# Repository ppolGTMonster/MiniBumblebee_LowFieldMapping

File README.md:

# Easy Scalable, Low-Cost Open Source Magnetic Field Detection System for Evaluating Low-Field MRI Magnets using a Motion Tracked Robot

## Author:
Pavel Povolni <pavel.povolni@tuebingen.mpg.de>

## Other Contributors to this hard- and software:
Felix Glang
  *  https://github.com/fglang
  * helped with the optimizers to design the hardware (fmincon & genetic)

Praveen Valsala
  * https://github.com/praveenivp
  * helped with reconstruction of MRI Data

Florian Birk
  * https://github.com/birkfl
  * helped with the Motion Tracking & the openCV Library

Sergej Maltsev
  * https://github.com/TheWinterProgrammer
  * helped with the Hardware 

## How to use

We tried our best to make the hardware as reproducible as possible and to develop the software without expensive extra toolboxes in Matlab (data evaluation), Python (motion tracking) and C++ (embedded code).
The PCBs were designed in KiCad 7 (free).
The mechanical components were designed with Autodesk Inventor 2021, although the Step files can be opened in any other CAD tool.

To get you started with the project as easily as possible, there are 4 instruction pdf's:
* Hallsensor (description of hardware & software for the hall sensor and calibration)
* Robot (description of the hardware & software for the robot used, including control)
* Motion tracking (description of the motion tracking setup & camera, including calibration)
* Mapping (description of the measurement process)

## Name
We always refer to this robot as Mini-Bumblebee in our team. The “big” Bumblebee refers to the large cubic robot that was built. Bumblebee itself stands for:
* B-Field
* Unterstanding and
* Mapping using
* Benchmarked
* Localized Hall
* Effect-based 
* Background
* Estimation and
* Evaluation

## Citing

If you use this code, please cite the corresponding paper:

Povolni, P., Bendfeld, R., Maltsev, S. et al. Easy scalable, low-cost open-source magnetic field detection system for evaluating low-field MRI magnets using a motion-tracked robot. Magn Reson Mater Phy (2025). https://doi.org/10.1007/s10334-025-01239-1

https://link.springer.com/article/10.1007/s10334-025-01239-1

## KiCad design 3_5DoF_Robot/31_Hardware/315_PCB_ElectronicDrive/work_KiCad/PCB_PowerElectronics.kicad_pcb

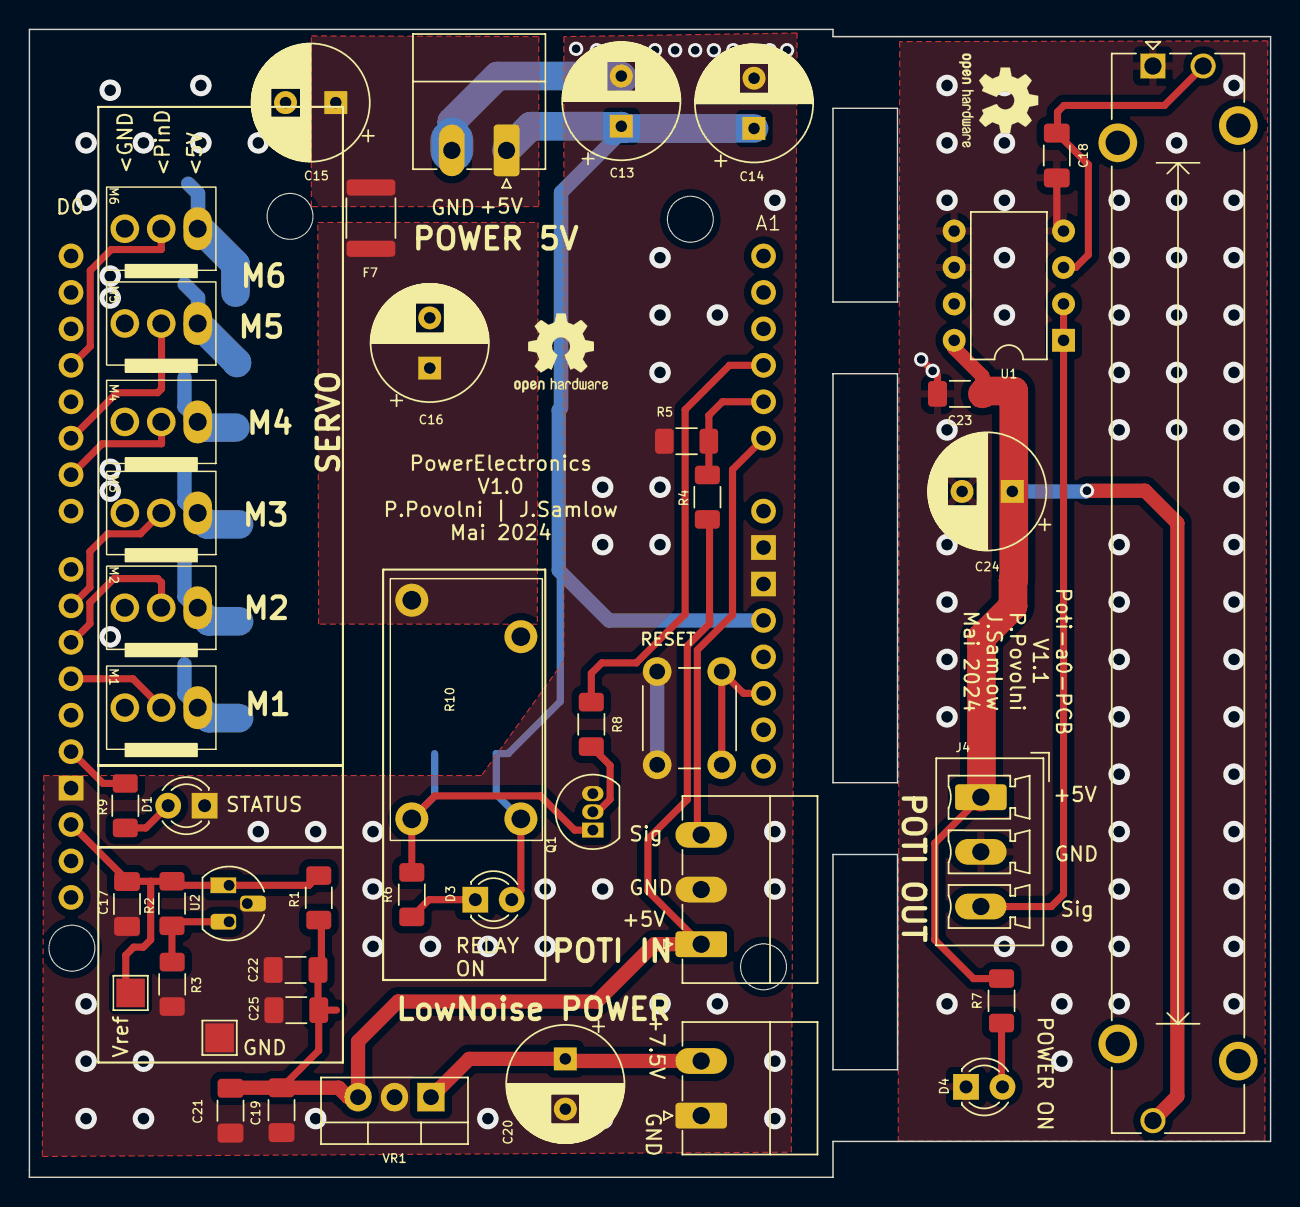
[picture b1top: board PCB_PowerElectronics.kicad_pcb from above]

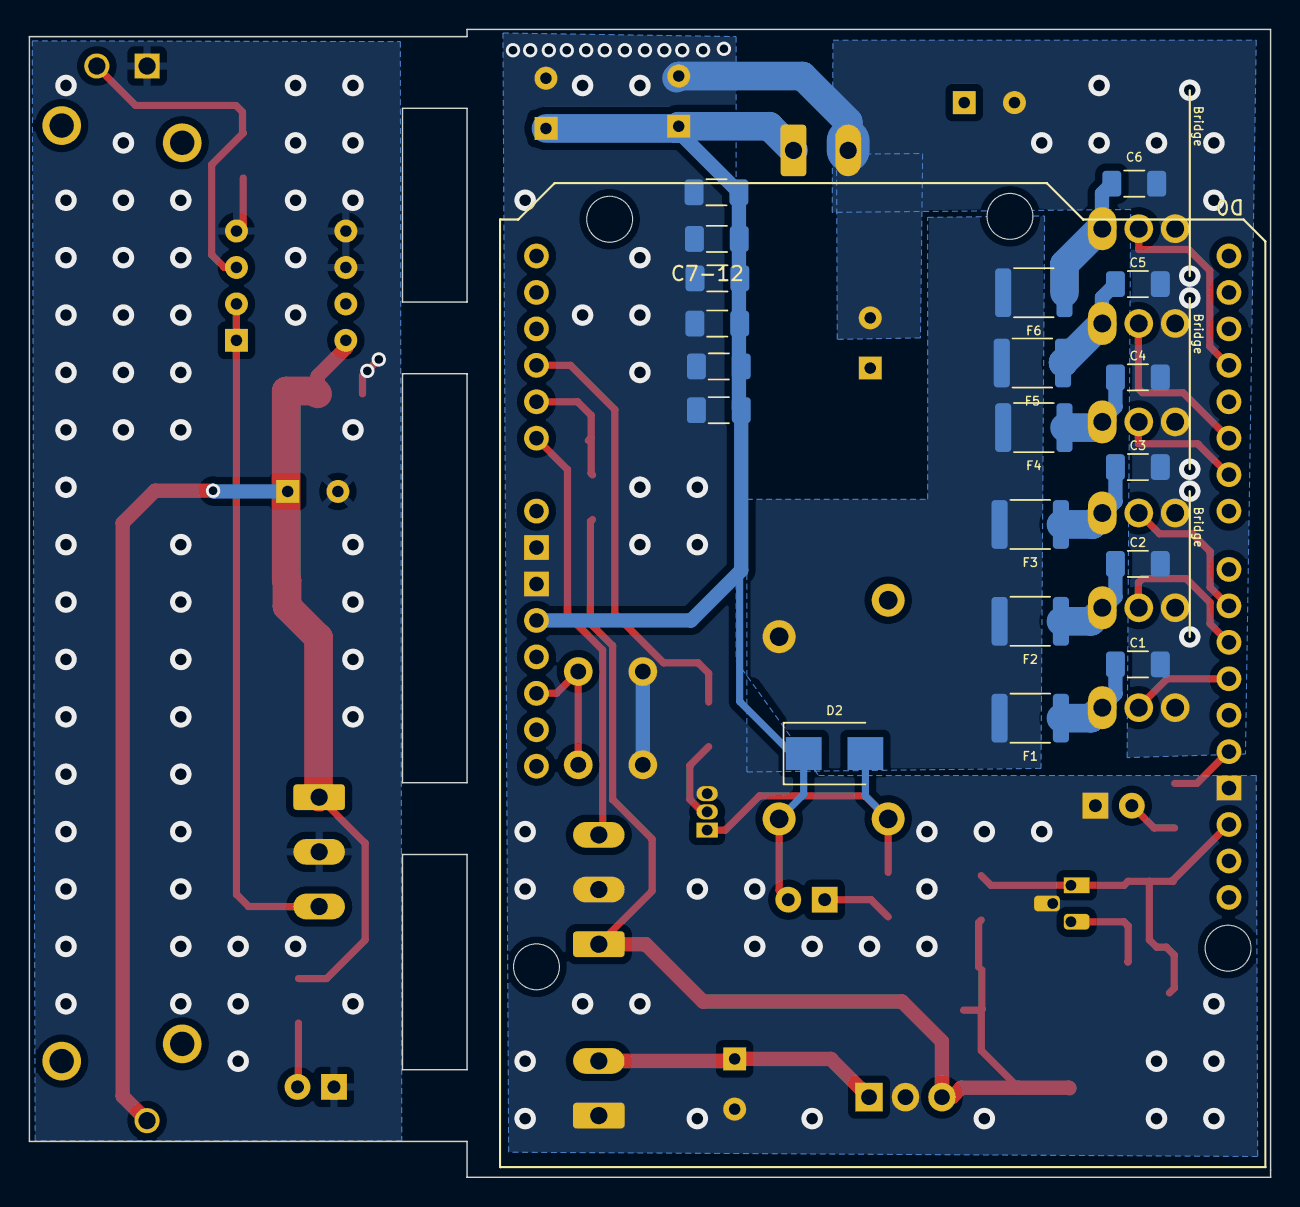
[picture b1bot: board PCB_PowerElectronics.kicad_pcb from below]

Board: 2 copper layers, 86.5 x 80.0 mm, 63 parts (19 on the bottom side), 32 nets.

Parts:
A1: Arduino_Uno; Arduino Uno Shield Mini BBB
C1, C2, C3, C4, C5, C6, C21, C25: 1µF; C_1206_3216Metric_Pad1.33x1.80mm_HandSolder
C7, C8, C9, C10, C11, C12: 100 n; C_1206_3216Metric_Pad1.33x1.80mm_HandSolder
C13, C15, C16: 47 µF; CP_Radial_D8.0mm_P3.50mm
C14, C20, C24: 47µF; CP_Radial_D8.0mm_P3.50mm
C17, C18, C19, C22, C23: 100n; C_1206_3216Metric_Pad1.33x1.80mm_HandSolder
D1: gelb; LED_D3.0mm
D2: S2A; D_SMB
D3: LED; LED_D3.0mm
D4: rot; LED_D3.0mm
F1: MF-MSMF 1100mA; Fuse_1812_4532Metric
F2, F3, F4: MF-MSMF 1100 mA; Fuse_1812_4532Metric
F5, F6, F7: MF-MSMF 750 mA; Fuse_1812_4532Metric
J1: 5V; PhoenixContact_MC_1,5_2-G-3.81_1x02_P3.81mm_Horizontal
J2: 7V; PhoenixContact_MC_1,5_2-G-3.81_1x02_P3.81mm_Horizontal
J3: Poti; PhoenixContact_MC_1,5_3-G-3.81_1x03_P3.81mm_Horizontal
J4: Poti; PhoenixContact_MCV_1,5_3-G-3.81_1x03_P3.81mm_Vertical
M1, M2, M3, M4, M5, M6: Molex_22272031; Molex_3Pin_Header
Q1: BC548A; TO-92_Inline
R1: 147, E192; R_1206_3216Metric_Pad1.30x1.75mm_HandSolder
R2: 1210, E192; R_1206_3216Metric_Pad1.30x1.75mm_HandSolder
R3, R4, R5: 2370, E192; R_1206_3216Metric_Pad1.30x1.75mm_HandSolder
R6, R7, R9: 147; R_1206_3216Metric_Pad1.30x1.75mm_HandSolder
R8: 1k; R_1206_3216Metric_Pad1.30x1.75mm_HandSolder
R10: Relay_AHQSH105LM100G
RV1: Poti; Potentiometer_Bourns_PTA6043_Single_Slide
SW1: RESET; SW_PUSH_6mm
U1: LM358; DIP-8_W7.62mm
U2: TL431C; TO-92_HandSolder
VR1: 7805; TO-220-3_Vertical

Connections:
+5V: A1.5V1 (5V), C7.1, C8.1, C9.1, C10.1, C11.1, C12.1, C13.1, C14.1, C15.1, D2.1 (K), D3.2 (A), F7.1, J1.1, R10.1
+5VA: C19.1, C21.1, C22.1, C23.1, C24.1, C25.1, J3.3, J4.1, R1.1, R4.1, R7.1, RV1.3, U1.8 (V+), VR1.3 (VO)
+5V/ Fused: C16.1, F7.2, R10.3
+5V/ Mot: F1.2, F2.2, F3.2, F4.2, F5.2, F6.2, R10.4
+7.5V: C20.1, J2.2, VR1.1 (VI)
/3,722 V (Aref): A1.AREF, C17.1, R1.2, R2.1, U2.3 (K)
/A0: A1.A0, J3.1
/A1: A1.A1, R4.2, R5.1
/A2: A1.A2, R8.1
/D3: A1.D3 (D3_INT1), M6.2
/D5: A1.D5, M5.2
/D6: A1.D6, M4.2
/D9: A1.D9, M3.2
/D10: A1.D10 (D10_CS), M2.2
/D11: A1.D11, M1.2
/D13: A1.D13, R9.1
/Poti/Pin A0: J4.3, U1.1, U1.2 (-)
GND: A1.GND1 (GND), A1.GND2 (GND), A1.GND3 (GND), C1.2, C2.2, C3.2, C4.2, C5.2, C6.2, C7.2, C8.2, C9.2, C10.2, C11.2, C12.2, C13.2, C14.2, C15.2, C16.2, C17.2, C18.2, C19.2, C20.2, C21.2, C22.2, C23.2, C24.2, C25.2, D1.1 (K), D4.1 (K), J1.2, J2.1, J3.2, J4.2, M1.3, M2.3, M3.3, M4.3, M5.3, M6.3, Q1.3 (E), R3.2, R5.2, RV1.1, SW1.2 (D), U1.4 (V-), U1.5 (+), U1.6 (-), U2.2 (A), VR1.2 (GND)
unnamed: A1.RST1 (RESET), SW1.1 (C)
unnamed: D1.2 (A), R9.2
unnamed: D2.2 (A), Q1.1 (C), R6.2, R10.2
unnamed: D3.1 (K), R6.1
unnamed: D4.2 (A), R7.2
unnamed: C1.1, F1.1, M1.1
unnamed: C2.1, F2.1, M2.1
unnamed: C3.1, F3.1, M3.1
unnamed: C4.1, F4.1, M4.1
unnamed: C5.1, F5.1, M5.1
unnamed: C6.1, F6.1, M6.1
unnamed: Q1.2 (B), R8.2
unnamed: C18.1, RV1.2, U1.3 (+)
unnamed: R2.2, R3.1, U2.1 (REF)

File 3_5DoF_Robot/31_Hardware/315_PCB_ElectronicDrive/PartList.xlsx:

Order list for electronic components
ID | Part-Info | Manufacturer | Part# Manufacturer | Part# Mouser | Amount | Comment
A1 | Arduino Uno | Arduino | A000073 | 782-A000073 | 1 | Doesn't need to be original Uno. Any copy will work too (eg from Seeed/Adafruit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
A1-2/1 | Pin-Header for Shield, 6pin | Preci-dip | 801-87-006-53-001101 | 437-8018700653001101 | 1
A1-2/2 | Pin-Header for Shield, 8pin | Preci-dip | 801-87-008-53-001101 | 437-8018700853001101 | 2
A1-2/3 | Pin-Header for Shield, 10pin | Preci-dip | 801-87-010-53-001101 | 437-8018701053001101 | 1
C11,C10,C8,C9,C12,C7,C18,C22,C19,C17,C23 | C 100n SMD1206 | KEMET | C1206C104M5RACTU | 80-C1206C104M5R | 11
C16,C15,C13 | C 47uF, Radial Elko | Wurth Elektronik | 860080674005 | 710-860080674005 | 6
C25,C21,C4,C6,C3,C1,C2,C5 | C 1uF SMD1206 | KEMET | C1206C105K4RAC | 80-C1206C105K4RAC | 8
D1 | LED 3mm | Wurth Elektronik | 151031VS06000 | 710-151031VS06000 | 3
D2 | Rectifiers 50V 1.5a S2A | onsemi / Fairchild | S2A | 512-S2A | 1
F4,F3,F2, F1 | Resettable Fuses - PPTC 6V 1.1A-HD 40A MAX | Bourns | MF-MSMF110-2 | 652-MF-MSMF110-2 | 4
F7,F6,F5 | Resettable Fuses - PPTC 13.2V .75A-HD 100A MAX | Bourns | MF-MSMF075-2 | 652-MF-MSMF075-2 | 3
J1 | Connector Power PCB (Male) | Phoenix Contact | 1803277 | 651-1803277 | 2
J1-2 | Connector Power Wire (Female) |  | 1803578 | 651-1803578 | 2
J3 | Connector Base PCB (Male) | Phoenix Contact | 1803280 | 651-1803280 | 1
J3/J4-2 | Connector Sensor Wire (Female) | Phoenix Contact | 1803581 | 651-1803581 | 2
J4 | Connector Sensor PCB (Male) | Phoenix Contact | 1803439 | 651-1803439 | 1
M3,M5,M2,M4,M6,M1 | Conenctor Stepper Motors | Molex | 22-27-2031 | 538-22-27-2031 | 6 | This connector fits exactly to the wiring of the robot used (Tinkercad Braccio 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
Q1 | BJT npn BC548A | Diotec Semiconductor | BC548A | 637-BC548A | 1
R1 | R 147Ohm , Precise, E196 | Panasonic | ERA-8AEB1470V | 667-ERA-8AEB1470V | 1
R10 | Relay, 10A, 5V Coil | Amphenol Anytek | AHQSH105LM100G | 523-AHQSH105LM100G | 1
R2 | R 1210 Ohm , Precise, E196 | Panasonic | ERA-8AEB1211V | 667-ERA-8AEB1211V | 1
R4,R3,R5 | R 2370 Ohm , Precise, E196 | Panasonic | ERA-8AEB2371V | 667-ERA-8AEB2371V | 3
R8 | R 1 kOhm | YAGEO | RC1206FR-101KL | 603-RC1206FR-101KL | 1
R9,R7,R6 | R 147 Ohm | KOA Speer | RK73H2BTTD1470F | 660-RK73H2BTTD1470F | 3
RV1 | Sliding potentiometer | Bourns | PTA6043-2015DPB103 | 652-PTA60432015DPB10 | 1
SW1 | Reset Push Button | CUI Devices | TS04-66-73-BK-260-SMT | 179-TS046673BK260SMT | 1
U1 | OpAmp TI LM358 | Texas Instruments | LM358P | 595-LM358P | 1
U2 | Voltage References TL431C | onsemi | TL431CLPRPG | 863-TL431CLPRPG | 1
VR1 | Linear Voltage Regulators 5V 500mA Positive 7805 | onsemi | MC78M05CTG | 863-MC78M05CTG | 1

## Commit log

2024-12-17 Small Fixes in Comments
2025-01-22 Added newer Manuals
2025-08-28 Updated a lot: * Added 6_Documentation (editable Docs) * Changed Path to original Robot from TinkerCAD (link to their files) * Edited the PartLists and added all mechanical Components * Added an exam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
2025-08-28 Update License_MIT.txt
    Updated License Infos
